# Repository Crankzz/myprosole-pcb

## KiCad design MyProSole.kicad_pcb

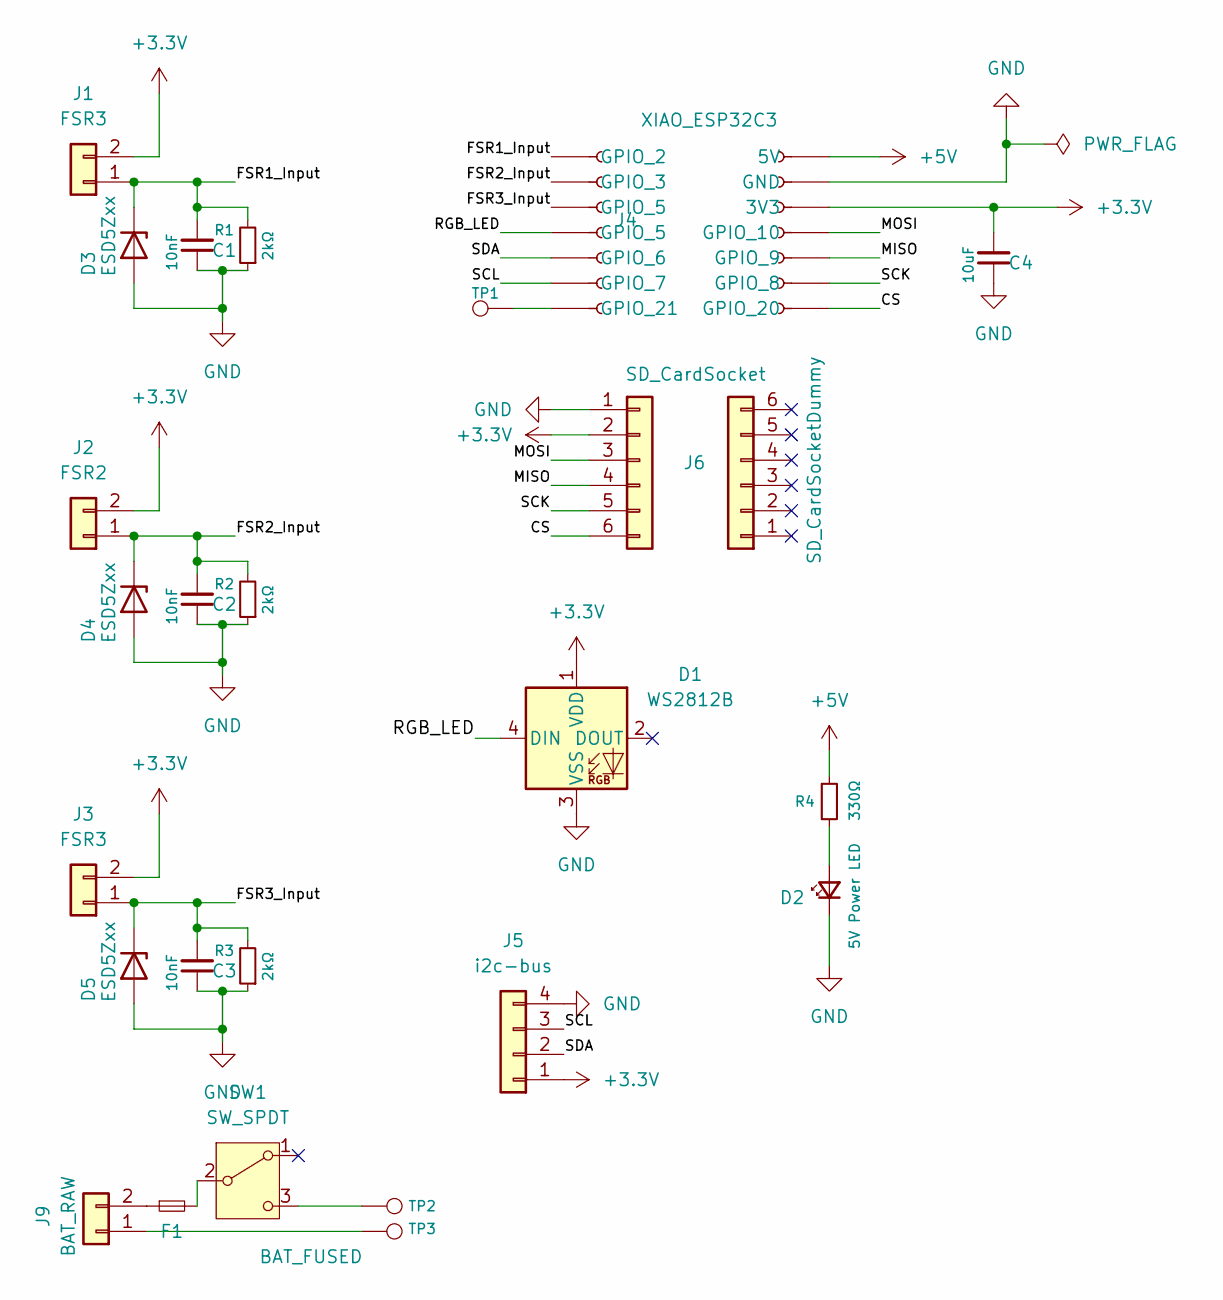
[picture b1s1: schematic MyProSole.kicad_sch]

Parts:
C1, C2, C3: 10nF; C_0805_2012Metric_Pad1.18x1.45mm_HandSolder
C4: 10uF; C_0805_2012Metric_Pad1.18x1.45mm_HandSolder
D1: WS2812B; LED_WS2812B_PLCC4_5.0x5.0mm_P3.2mm
D2: 5V Power LED; LED_miniPLCC_2315_Handsoldering
D3, D4, D5: ESD5Zxx; D_SOD-523
F1: BAT_FUSED; Fuse_1206_3216Metric_Pad1.42x1.75mm_HandSolder
J1, J3: FSR3; JST_XH_B2B-XH-AM_1x02_P2.50mm_Vertical
J2: FSR2; JST_XH_B2B-XH-AM_1x02_P2.50mm_Vertical
J4: Conn_01x07_Socket_XIAO_ESP32C3_Left; PinSocket_1x07_P2.54mm_Vertical
J5: i2c-bus; JST_XH_B4B-XH-AM_1x04_P2.50mm_Vertical
J6: SD_CardSocket; PinSocket_1x06_P2.54mm_Vertical
J7: XIAO_ESP32C3; PinSocket_1x07_P2.54mm_Vertical
J8: SD_CardSocketDummy; PinSocket_1x06_P2.54mm_Vertical
J9: BAT_RAW; JST_PH_B2B-PH-K_1x02_P2.00mm_Vertical
R1, R2, R3: 2kΩ; R_0805_2012Metric_Pad1.20x1.40mm_HandSolder
R4: 330Ω; R_0805_2012Metric_Pad1.20x1.40mm_HandSolder
SW1: SW_SPDT; WS-SLTU THT Mini Slide Switch
TP1, TP2, TP3: TestPoint; TestPoint_Pad_2.0x2.0mm

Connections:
+3.3V: C4.2, D1.1 (VDD), J1.2, J2.2, J3.2, J5.1, J6.2, J7.5 (3V3)
+5V: J7.7 (5V), R4.1
/CS: J6.6, J7.1 (GPIO_20)
/FSR1_Input: C1.2, D3.1 (K), J1.1, J4.1 (GPIO_2), R1.2
/FSR2_Input: C2.2, D4.1 (K), J2.1, J4.2 (GPIO_3), R2.2
/FSR3_Input: C3.2, D5.1 (K), J3.1, J4.3 (GPIO_5), R3.2
/MISO: J6.4, J7.3 (GPIO_9)
/MOSI: J6.3, J7.4 (GPIO_10)
/RGB_LED: D1.4 (DIN), J4.4 (GPIO_5)
/SCK: J6.5, J7.2 (GPIO_8)
/SCL: J4.6 (GPIO_7), J5.3
/SDA: J4.5 (GPIO_6), J5.2
GND: C1.1, C2.1, C3.1, C4.1, D1.3 (VSS), D2.1 (K), D3.2 (A), D4.2 (A), D5.2 (A), J5.4, J6.1, J7.6 (GND), R1.1, R2.1, R3.1
unnamed: D2.2 (A), R4.2
unnamed: J4.7 (GPIO_21), TP1.1 (1_1)
unnamed: J9.1, TP3.1 (1_1)
unnamed: F1.1, J9.2
unnamed: F1.2, SW1.2 (B)
unnamed: SW1.3 (C), TP2.1 (1_1)

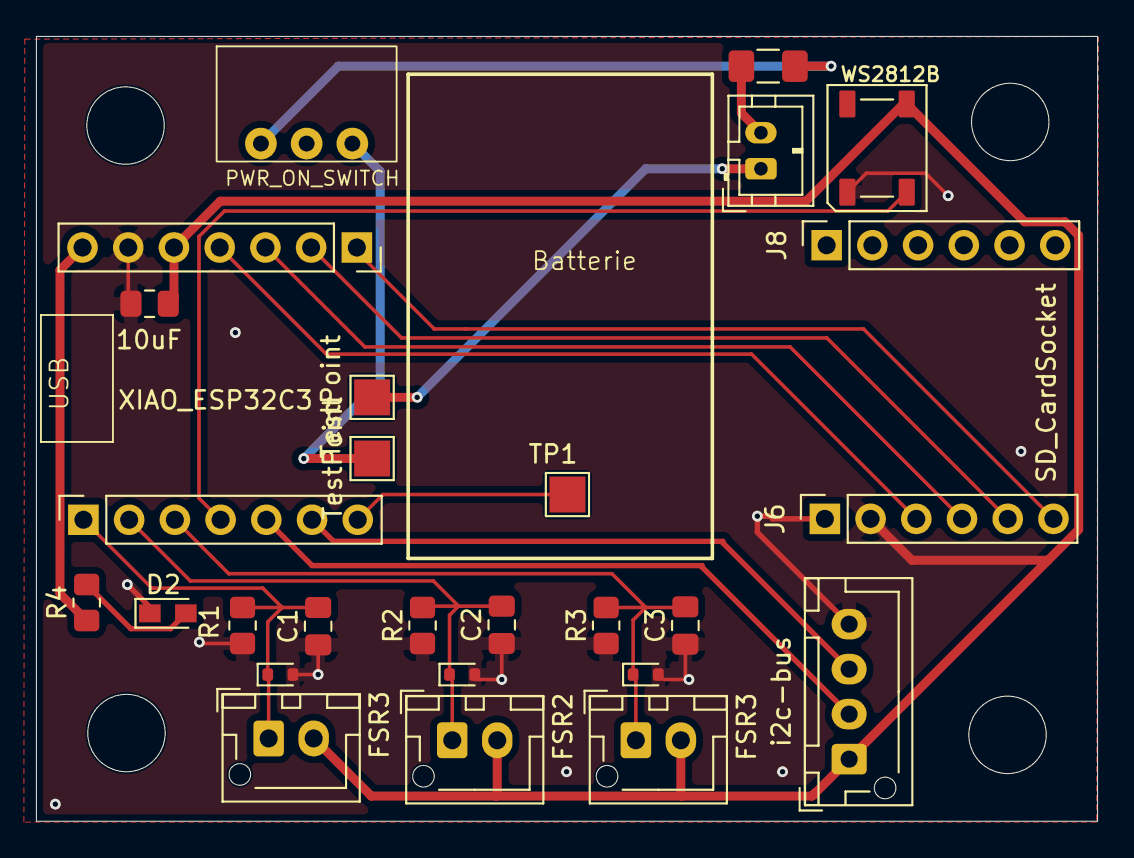
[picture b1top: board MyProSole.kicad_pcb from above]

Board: 2 copper layers, 58.9 x 43.6 mm, 27 parts (0 on the bottom side), 19 nets.

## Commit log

2025-12-02 Init KiCad PCB
2025-12-08 Schaltplan Teil 1 fertig
2025-12-08 Fix ERC ES2812 LED Dout
2025-12-09 Fix ERC
2025-12-09 Only some designed changes
2025-12-09 Added 5V led, Helper Socket for SD_Card & Footprints Added
2025-12-09 Started Layout
2025-12-09 First Step for Layout
2025-12-09 New arragement
2025-12-09 almost ready for review
2025-12-10 Versoin bevor review
2025-12-10 Added Revisoin Version & Date on Backplate
2026-01-05 first prototyp versions
2026-01-05 Added ESP Step
2026-01-05 Fixed ESP32_C3 3D Model
2026-01-06 Removed Old Step
2026-01-06 Added two new 3D Models for ESP32
2026-01-06 Added ESP for 3dmodel to pcb
2026-01-07 Added all 3d model files
2026-01-12 Version 1.1
2026-01-27 Last push from Tuxedo
2026-06-24 Swap SD Card GND and 3V3
